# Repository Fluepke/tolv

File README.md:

# Tolv

A work-in-progress digital lighting artwork

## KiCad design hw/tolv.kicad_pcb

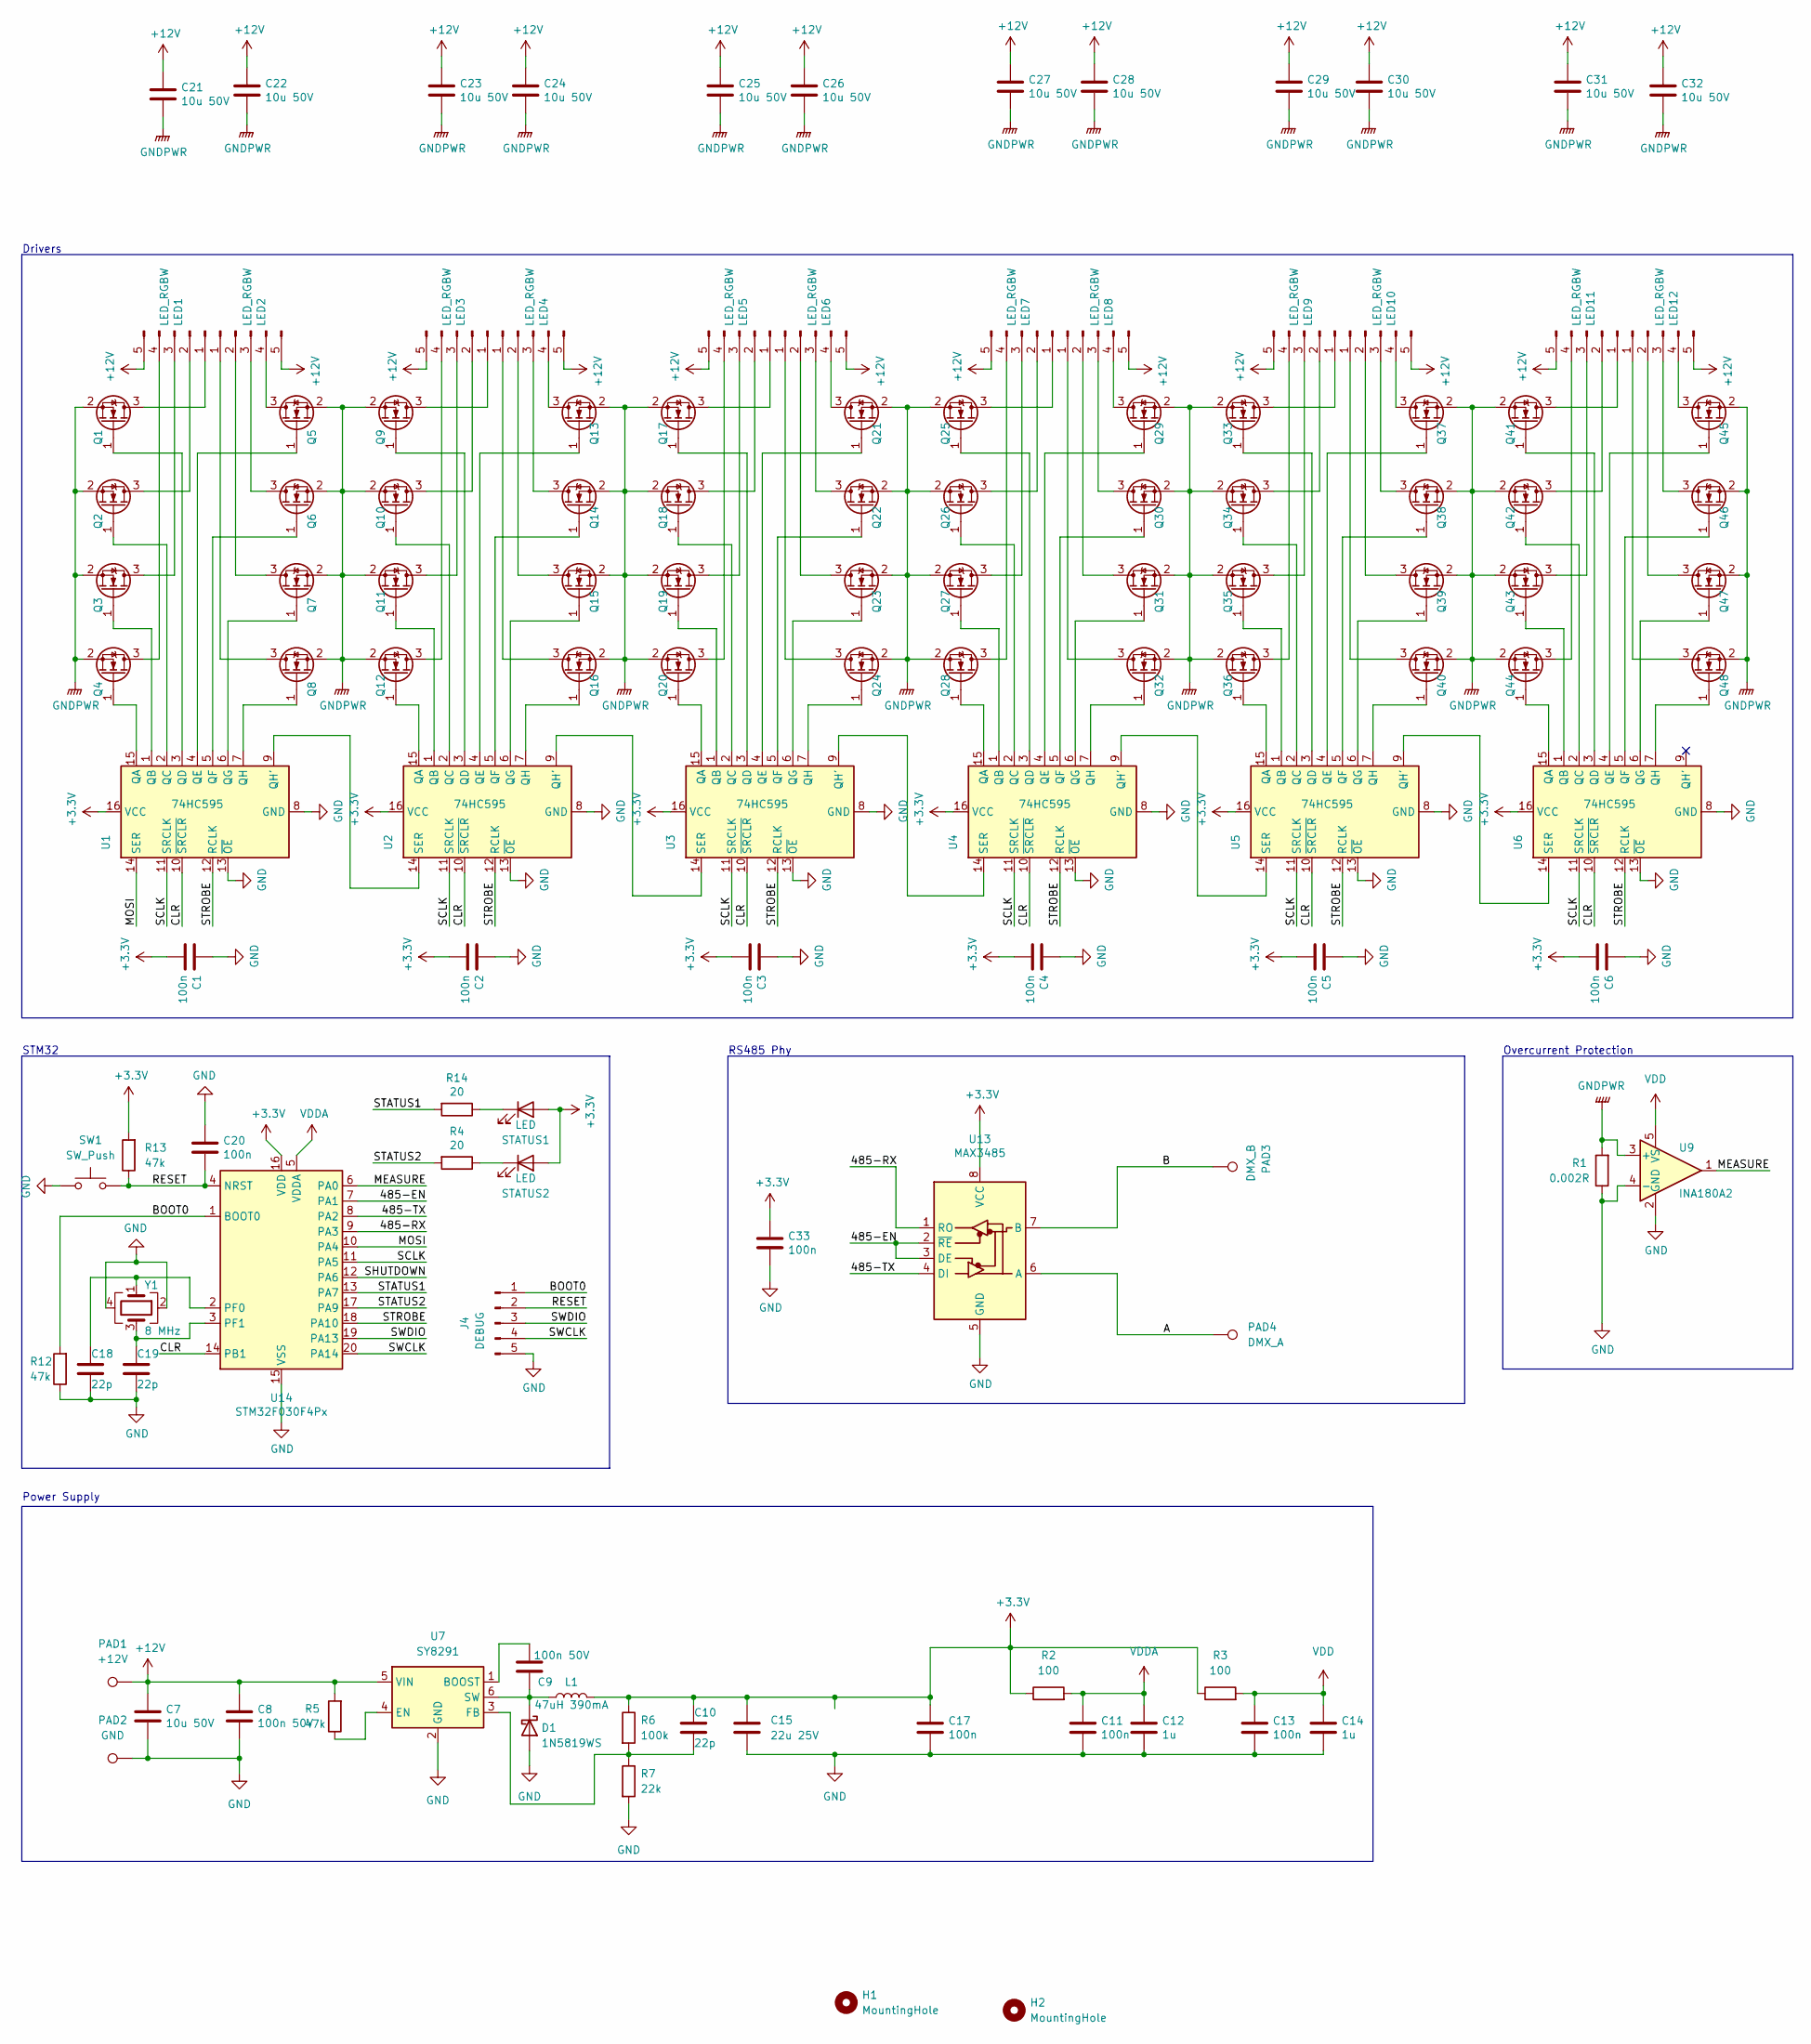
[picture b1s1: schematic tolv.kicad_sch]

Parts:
C1, C2, C3, C4, C5, C6, C11, C13, C17, C20, C33: 100n; C_0402_1005Metric; LCSC C1525
C7, C21, C22, C23, C24, C25, C26, C27, C28, C29, C30, C31, C32: 10u 50V; C_1206_3216Metric; LCSC C13585
C8, C9: 100n 50V; C_0402_1005Metric; LCSC C307331
C10, C18, C19: 22p; C_0402_1005Metric; LCSC C1555
C12, C14: 1u; C_0402_1005Metric; LCSC C52923
C15: 22u 25V; C_0805_2012Metric; LCSC C45783
D1: 1N5819WS; D_SOD-323; LCSC C191023
H1, H2: MountingHole; MountingHole_3.2mm_M3
J4: DEBUG; JST_SH_BM05B-SRSS-TB_1x05-1MP_P1.00mm_Vertical; LCSC C239523
L1: 47uH 390mA; L_1210_3225Metric; LCSC C90318
LED1, LED2, LED3, LED4, LED5, LED6, LED7, LED8, LED9, LED10, LED11, LED12: LED_RGBW; JST_PH_B5B-PH-K_1x05_P2.00mm_Vertical; LCSC C2322
PAD1: +12V; TestPoint_Loop_D3.80mm_Drill2.0mm
PAD2: GND; TestPoint_Loop_D3.80mm_Drill2.0mm
PAD3: DMX_B; TestPoint_Loop_D3.80mm_Drill2.0mm
PAD4: DMX_A; TestPoint_Loop_D3.80mm_Drill2.0mm
Q1, Q2, Q3, Q4, Q5, Q6, Q7, Q8, Q9, Q10, Q11, Q12, Q13, Q14, Q15, Q16, Q17, Q18, Q19, Q20, Q21, Q22, Q23, Q24, Q25, Q26, Q27, Q28, Q29, Q30, Q31, Q32, Q33, Q34, Q35, Q36, Q37, Q38, Q39, Q40, Q41, Q42, Q43, Q44, Q45, Q46, Q47, Q48: AO3400A; SOT-23; LCSC C20917
R1: 0.002R; R_2512_6332Metric; LCSC C500614
R2, R3: 100; R_0402_1005Metric; LCSC C25076
R4, R14: 20; R_0402_1005Metric; LCSC C25087
R5, R12, R13: 47k; R_0402_1005Metric; LCSC C25792
R6: 100k; R_0402_1005Metric; LCSC C25086
R7: 22k; R_0402_1005Metric; LCSC C25768
STATUS1, STATUS2: LED; LED_0805_2012Metric; LCSC C34499
SW1: SW_Push; SW_SPST_B3U-1000P; LCSC C231329
U1, U2, U3, U4, U5, U6: 74HC595; SOIC-16_3.9x9.9mm_P1.27mm; LCSC C5947
U7: SY8291; TSOT-23-6; LCSC C125896
U9: INA180A2; SOT-23-5; LCSC C192764
U13: MAX3485; SOIC-8_3.9x4.9mm_P1.27mm; LCSC C8963
U14: STM32F030F4Px; TSSOP-20_4.4x6.5mm_P0.65mm; LCSC C32908
Y1: 8 MHz; Crystal_SMD_3225-4Pin_3.2x2.5mm; LCSC C9002

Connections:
+3V3: C1.2, C2.2, C3.2, C4.2, C5.2, C6.2, C10.1, C15.1, C17.1, C33.1, L1.2, R2.1, R3.1, R6.1, R13.2, STATUS1.2 (A), STATUS2.2 (A), U1.16 (VCC), U2.16 (VCC), U3.16 (VCC), U4.16 (VCC), U5.16 (VCC), U6.16 (VCC), U13.8 (VCC), U14.16 (VDD); also elsewhere on the board
+12V: C7.1, C8.1, C21.1, C22.1, C23.1, C24.1, C25.1, C26.1, C27.1, C28.1, C29.1, C30.1, C31.1, C32.1, LED1.5, LED2.5, LED3.5, LED4.5, LED5.5, LED6.5, LED7.5, LED8.5, LED9.5, LED10.5, LED11.5, LED12.5, PAD1.1, R5.2, U7.5 (VIN)
/485-EN: U13.2 (~RE), U13.3 (DE), U14.7 (PA1)
/485-RX: U13.1 (RO), U14.9 (PA3)
/485-TX: U13.4 (DI), U14.8 (PA2)
/A: PAD4.1, U13.6 (A)
/B: PAD3.1, U13.7 (B)
/BOOT0: J4.1, R12.2, U14.1 (BOOT0)
/CLR: U1.10 (~SRCLR), U2.10 (~SRCLR), U3.10 (~SRCLR), U4.10 (~SRCLR), U5.10 (~SRCLR), U6.10 (~SRCLR), U14.14 (PB1)
/MEASURE: U9.1, U14.6 (PA0)
/MOSI: U1.14 (SER), U14.10 (PA4)
/RESET: C20.2, J4.2, R13.1, SW1.2, U14.4 (NRST)
/SCLK: U1.11 (SRCLK), U2.11 (SRCLK), U3.11 (SRCLK), U4.11 (SRCLK), U5.11 (SRCLK), U6.11 (SRCLK), U14.11 (PA5)
/SHUTDOWN: U14.12 (PA6)
/STATUS1: R14.2, U14.13 (PA7)
/STATUS2: R4.2, U14.17 (PA9)
/STROBE: U1.12 (RCLK), U2.12 (RCLK), U3.12 (RCLK), U4.12 (RCLK), U5.12 (RCLK), U6.12 (RCLK), U14.18 (PA10)
/SWCLK: J4.4, U14.20 (PA14)
/SWDIO: J4.3, U14.19 (PA13)
GND: C1.1, C2.1, C3.1, C4.1, C5.1, C6.1, C7.2, C8.2, C11.2, C12.2, C13.2, C14.2, C15.2, C17.2, C18.2, C19.2, C20.1, C33.2, D1.2 (A), J4.5, PAD2.1, R1.1, R7.2, R12.1, SW1.1, U1.8 (GND), U1.13 (~OE), U2.8 (GND), U2.13 (~OE), U3.8 (GND), U3.13 (~OE), U4.8 (GND), U4.13 (~OE), U5.8 (GND), U5.13 (~OE), U6.8 (GND), U6.13 (~OE), U7.2 (GND), U9.2 (GND), U9.4 (-), U13.5 (GND), U14.15 (VSS), Y1.2, Y1.4
GNDPWR: C21.2, C22.2, C23.2, C24.2, C25.2, C26.2, C27.2, C28.2, C29.2, C30.2, C31.2, C32.2, Q1.2 (S), Q2.2 (S), Q3.2 (S), Q4.2 (S), Q5.2 (S), Q6.2 (S), Q7.2 (S), Q8.2 (S), Q9.2 (S), Q10.2 (S), Q11.2 (S), Q12.2 (S), Q13.2 (S), Q14.2 (S), Q15.2 (S), Q16.2 (S), Q17.2 (S), Q18.2 (S), Q19.2 (S), Q20.2 (S), Q21.2 (S), Q22.2 (S), Q23.2 (S), Q24.2 (S), Q25.2 (S), Q26.2 (S), Q27.2 (S), Q28.2 (S), Q29.2 (S), Q30.2 (S), Q31.2 (S), Q32.2 (S), Q33.2 (S), Q34.2 (S), Q35.2 (S), Q36.2 (S), Q37.2 (S), Q38.2 (S), Q39.2 (S), Q40.2 (S), Q41.2 (S), Q42.2 (S), Q43.2 (S), Q44.2 (S), Q45.2 (S), Q46.2 (S), Q47.2 (S), Q48.2 (S), R1.2, U9.3 (+)
unnamed: C9.1, D1.1 (K), L1.1, U7.6 (SW)
unnamed: C9.2, U7.1 (BOOST)
unnamed: C10.2, R6.2, R7.1, U7.3 (FB)
unnamed: C18.1, U14.2 (PF0), Y1.1
unnamed: C19.1, U14.3 (PF1), Y1.3
unnamed: LED1.1, Q1.3 (D)
unnamed: LED1.2, Q2.3 (D)
unnamed: LED1.3, Q3.3 (D)
unnamed: LED1.4, Q4.3 (D)
unnamed: LED2.1, Q8.3 (D)
unnamed: LED2.2, Q7.3 (D)
unnamed: LED2.3, Q6.3 (D)
unnamed: LED2.4, Q5.3 (D)
unnamed: LED3.1, Q9.3 (D)
unnamed: LED3.2, Q10.3 (D)
unnamed: LED3.3, Q11.3 (D)
unnamed: LED3.4, Q12.3 (D)
unnamed: LED4.1, Q16.3 (D)
unnamed: LED4.2, Q15.3 (D)
unnamed: LED4.3, Q14.3 (D)
unnamed: LED4.4, Q13.3 (D)
unnamed: LED5.1, Q17.3 (D)
unnamed: LED5.2, Q18.3 (D)
unnamed: LED5.3, Q19.3 (D)
unnamed: LED5.4, Q20.3 (D)
unnamed: LED6.1, Q24.3 (D)
unnamed: LED6.2, Q23.3 (D)
unnamed: LED6.3, Q22.3 (D)
unnamed: LED6.4, Q21.3 (D)
unnamed: LED7.1, Q25.3 (D)
unnamed: LED7.2, Q26.3 (D)
unnamed: LED7.3, Q27.3 (D)
unnamed: LED7.4, Q28.3 (D)
unnamed: LED8.1, Q32.3 (D)
unnamed: LED8.2, Q31.3 (D)
unnamed: LED8.3, Q30.3 (D)
unnamed: LED8.4, Q29.3 (D)
unnamed: LED9.1, Q33.3 (D)
unnamed: LED9.2, Q34.3 (D)
unnamed: LED9.3, Q35.3 (D)
unnamed: LED9.4, Q36.3 (D)
unnamed: LED10.1, Q40.3 (D)
unnamed: LED10.2, Q39.3 (D)
unnamed: LED10.3, Q38.3 (D)
unnamed: LED10.4, Q37.3 (D)
unnamed: LED11.1, Q41.3 (D)
unnamed: LED11.2, Q42.3 (D)
unnamed: LED11.3, Q43.3 (D)
unnamed: LED11.4, Q44.3 (D)
unnamed: LED12.1, Q48.3 (D)
unnamed: LED12.2, Q47.3 (D)
unnamed: LED12.3, Q46.3 (D)
unnamed: LED12.4, Q45.3 (D)
unnamed: Q1.1 (G), U1.3 (QD)
unnamed: Q2.1 (G), U1.2 (QC)
unnamed: Q3.1 (G), U1.1 (QB)
unnamed: Q4.1 (G), U1.15 (QA)
unnamed: Q5.1 (G), U1.4 (QE)
unnamed: Q6.1 (G), U1.5 (QF)
unnamed: Q7.1 (G), U1.6 (QG)
unnamed: Q8.1 (G), U1.7 (QH)
unnamed: Q9.1 (G), U2.3 (QD)
unnamed: Q10.1 (G), U2.2 (QC)
unnamed: Q11.1 (G), U2.1 (QB)
unnamed: Q12.1 (G), U2.15 (QA)
unnamed: Q13.1 (G), U2.4 (QE)
unnamed: Q14.1 (G), U2.5 (QF)
unnamed: Q15.1 (G), U2.6 (QG)
unnamed: Q16.1 (G), U2.7 (QH)
unnamed: Q17.1 (G), U3.3 (QD)
unnamed: Q18.1 (G), U3.2 (QC)
unnamed: Q19.1 (G), U3.1 (QB)
unnamed: Q20.1 (G), U3.15 (QA)
unnamed: Q21.1 (G), U3.4 (QE)
unnamed: Q22.1 (G), U3.5 (QF)
unnamed: Q23.1 (G), U3.6 (QG)
unnamed: Q24.1 (G), U3.7 (QH)
unnamed: Q25.1 (G), U4.3 (QD)
unnamed: Q26.1 (G), U4.2 (QC)
unnamed: Q27.1 (G), U4.1 (QB)
unnamed: Q28.1 (G), U4.15 (QA)
unnamed: Q29.1 (G), U4.4 (QE)
unnamed: Q30.1 (G), U4.5 (QF)
unnamed: Q31.1 (G), U4.6 (QG)
unnamed: Q32.1 (G), U4.7 (QH)
unnamed: Q33.1 (G), U5.3 (QD)
unnamed: Q34.1 (G), U5.2 (QC)
unnamed: Q35.1 (G), U5.1 (QB)
unnamed: Q36.1 (G), U5.15 (QA)
unnamed: Q37.1 (G), U5.4 (QE)
unnamed: Q38.1 (G), U5.5 (QF)
unnamed: Q39.1 (G), U5.6 (QG)
unnamed: Q40.1 (G), U5.7 (QH)
unnamed: Q41.1 (G), U6.3 (QD)
unnamed: Q42.1 (G), U6.2 (QC)
unnamed: Q43.1 (G), U6.1 (QB)
unnamed: Q44.1 (G), U6.15 (QA)
unnamed: Q45.1 (G), U6.4 (QE)
unnamed: Q46.1 (G), U6.5 (QF)
unnamed: Q47.1 (G), U6.6 (QG)
unnamed: Q48.1 (G), U6.7 (QH)
unnamed 122: R4.1, STATUS2.1 (K); also elsewhere on the board
unnamed: R5.1, U7.4 (EN)
unnamed 124: R14.1, STATUS1.1 (K); also elsewhere on the board
unnamed: U1.9 (QH'), U2.14 (SER)
unnamed: U2.9 (QH'), U3.14 (SER)
unnamed: U3.9 (QH'), U4.14 (SER)
unnamed: U4.9 (QH'), U5.14 (SER)
unnamed: U5.9 (QH'), U6.14 (SER)
VDD: C13.1, C14.1, R3.2, U9.5 (VS)
VDDA: C11.1, C12.1, R2.2, U14.5 (VDDA)

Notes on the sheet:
Power Supply
RS485 Phy
Drivers
Overcurrent Protection
STM32

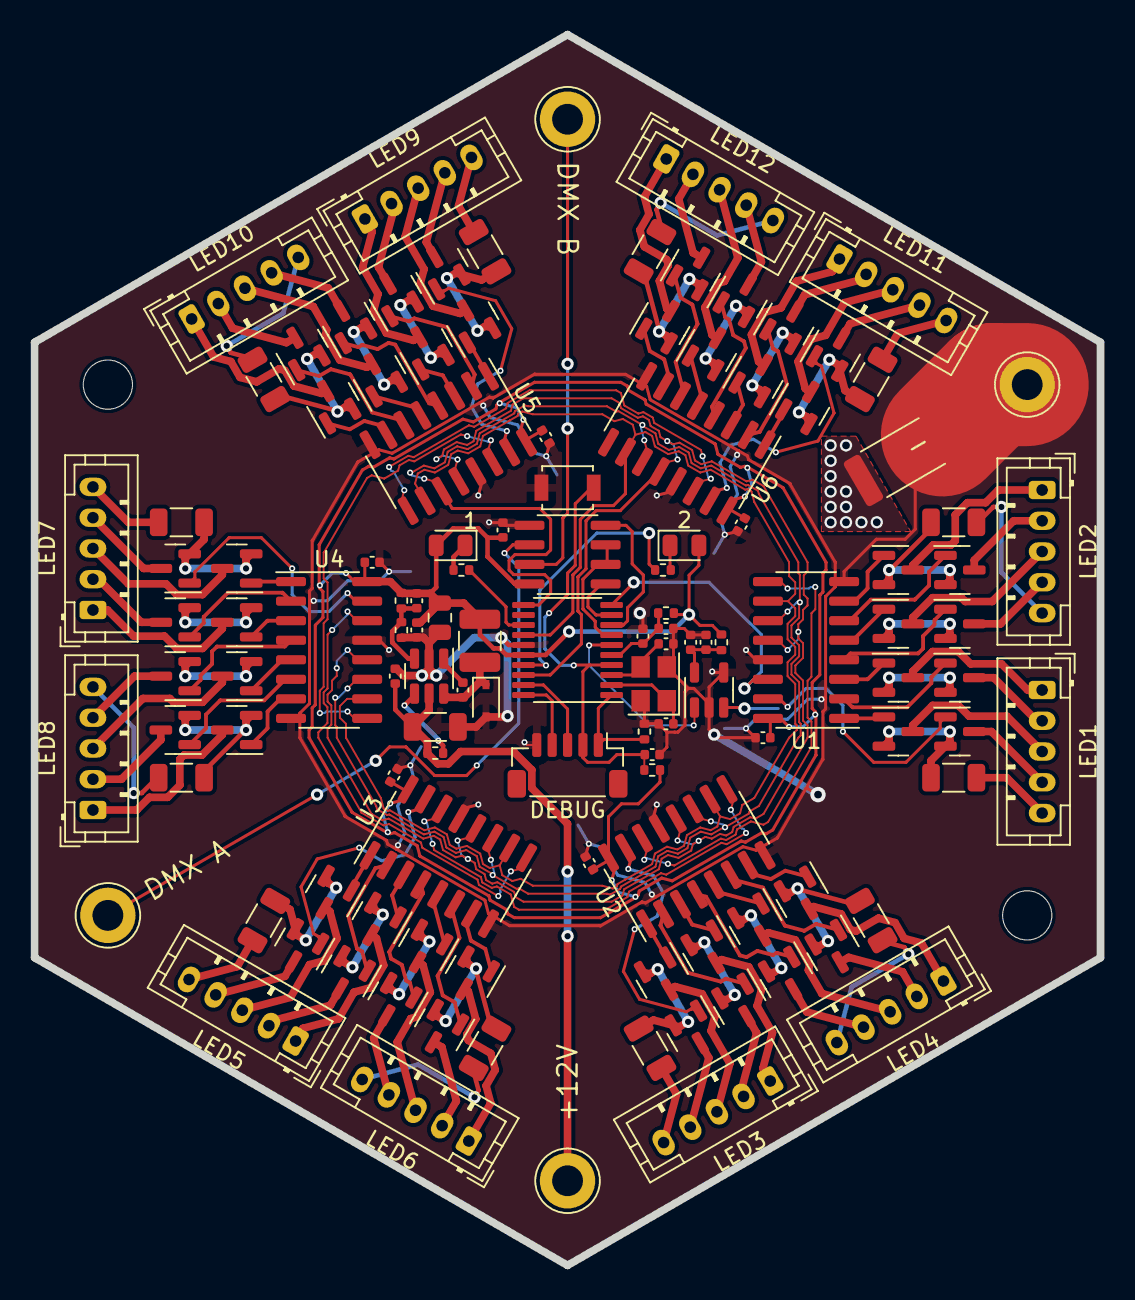
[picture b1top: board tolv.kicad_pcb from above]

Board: 2 copper layers, 69.3 x 80.0 mm, 125 parts (0 on the bottom side), 131 nets.

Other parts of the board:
1, 2: LED; LED_0805_2012Metric

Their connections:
+3V3: 1.2 (A), 2.2 (A); also elsewhere on the board
unnamed 122: 2.1 (K); also elsewhere on the board
unnamed 124: 1.1 (K); also elsewhere on the board

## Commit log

2022-01-26 Inital commit
2022-01-29 My first 3D design with OpenSCAD ✨
2022-01-30 Switch to switching regulator
2022-02-02 Update schematic
